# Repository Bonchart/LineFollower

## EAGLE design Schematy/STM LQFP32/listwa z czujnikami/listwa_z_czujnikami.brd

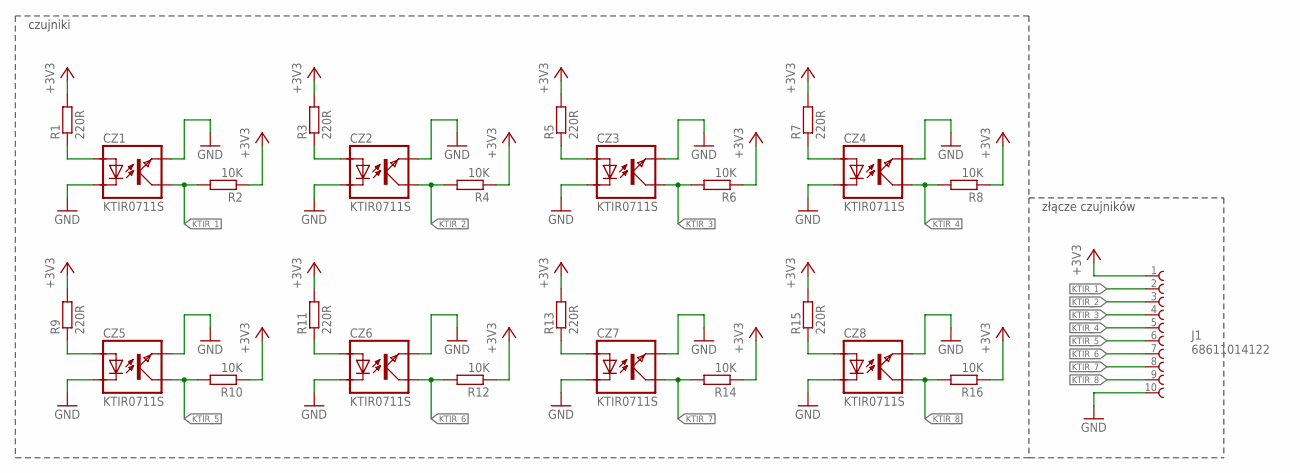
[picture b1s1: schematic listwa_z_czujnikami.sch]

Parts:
CZ1, CZ2, CZ3, CZ4, CZ5, CZ6, CZ7, CZ8: KTIR0711S; TOP
J1: 68611014122
R1, R3, R5, R7, R9, R11, R13, R15: 220R; R0805
R2, R4, R6, R8, R10, R12, R14, R16: 10K; R0805

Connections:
+3V3: J1.1, R1.2, R2.1, R3.2, R4.1, R5.2, R6.1, R7.2, R8.1, R9.2, R10.1, R11.2, R12.1, R13.2, R14.1, R15.2, R16.1
GND: CZ1.EMITER, CZ1.KATODA, CZ2.EMITER, CZ2.KATODA, CZ3.EMITER, CZ3.KATODA, CZ4.EMITER, CZ4.KATODA, CZ5.EMITER, CZ5.KATODA, CZ6.EMITER, CZ6.KATODA, CZ7.EMITER, CZ7.KATODA, CZ8.EMITER, CZ8.KATODA, J1.10
KTIR_1: CZ1.KOLEKTOR, J1.2, R2.2
KTIR_2: CZ2.KOLEKTOR, J1.3, R4.2
KTIR_3: CZ3.KOLEKTOR, J1.4, R6.2
KTIR_4: CZ4.KOLEKTOR, J1.5, R8.2
KTIR_5: CZ5.KOLEKTOR, J1.6, R10.2
KTIR_6: CZ6.KOLEKTOR, J1.7, R12.2
KTIR_7: CZ7.KOLEKTOR, J1.8, R14.2
KTIR_8: CZ8.KOLEKTOR, J1.9, R16.2
unnamed: CZ2.ANODA, R3.1
unnamed: CZ1.ANODA, R1.1
unnamed: CZ3.ANODA, R5.1
unnamed: CZ4.ANODA, R7.1
unnamed: CZ5.ANODA, R9.1
unnamed: CZ6.ANODA, R11.1
unnamed: CZ7.ANODA, R13.1
unnamed: CZ8.ANODA, R15.1

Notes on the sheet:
czujniki
złącze czujników

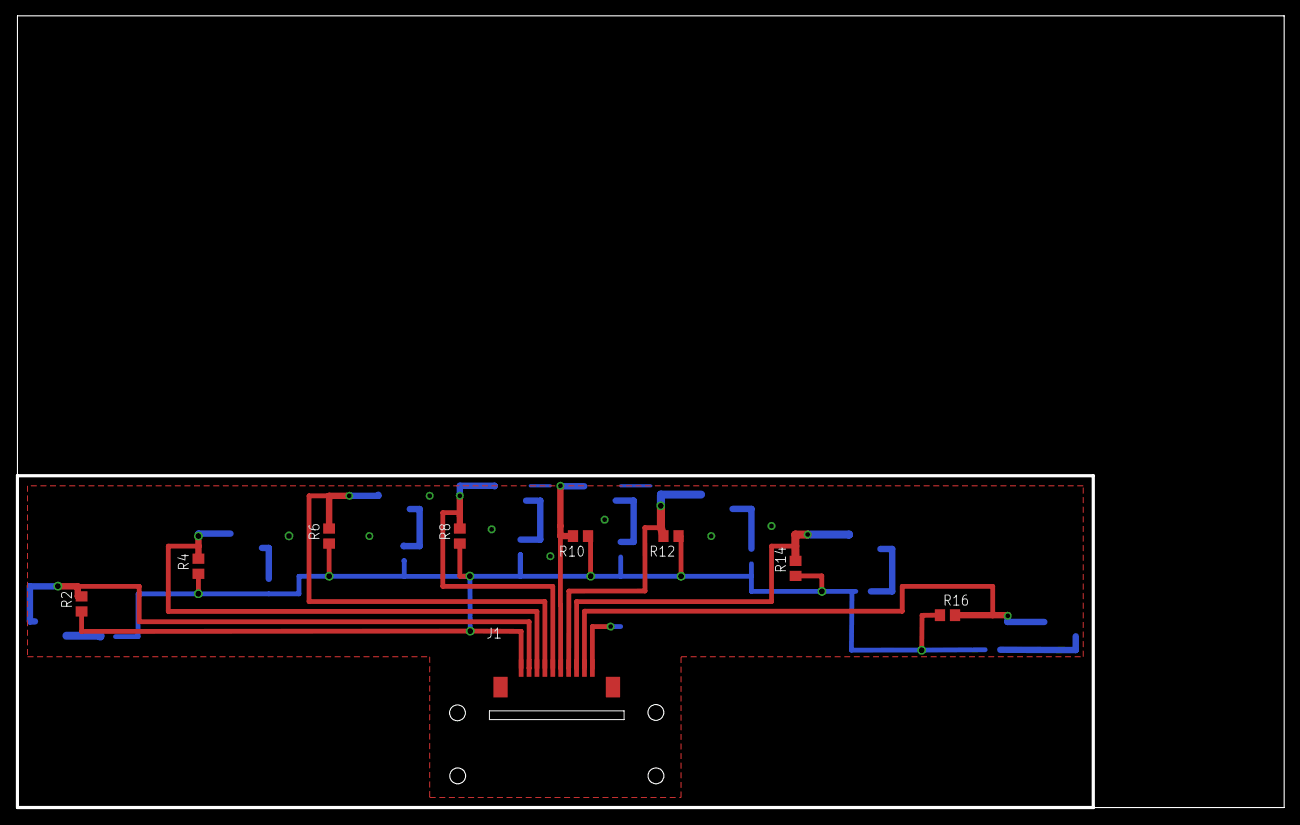
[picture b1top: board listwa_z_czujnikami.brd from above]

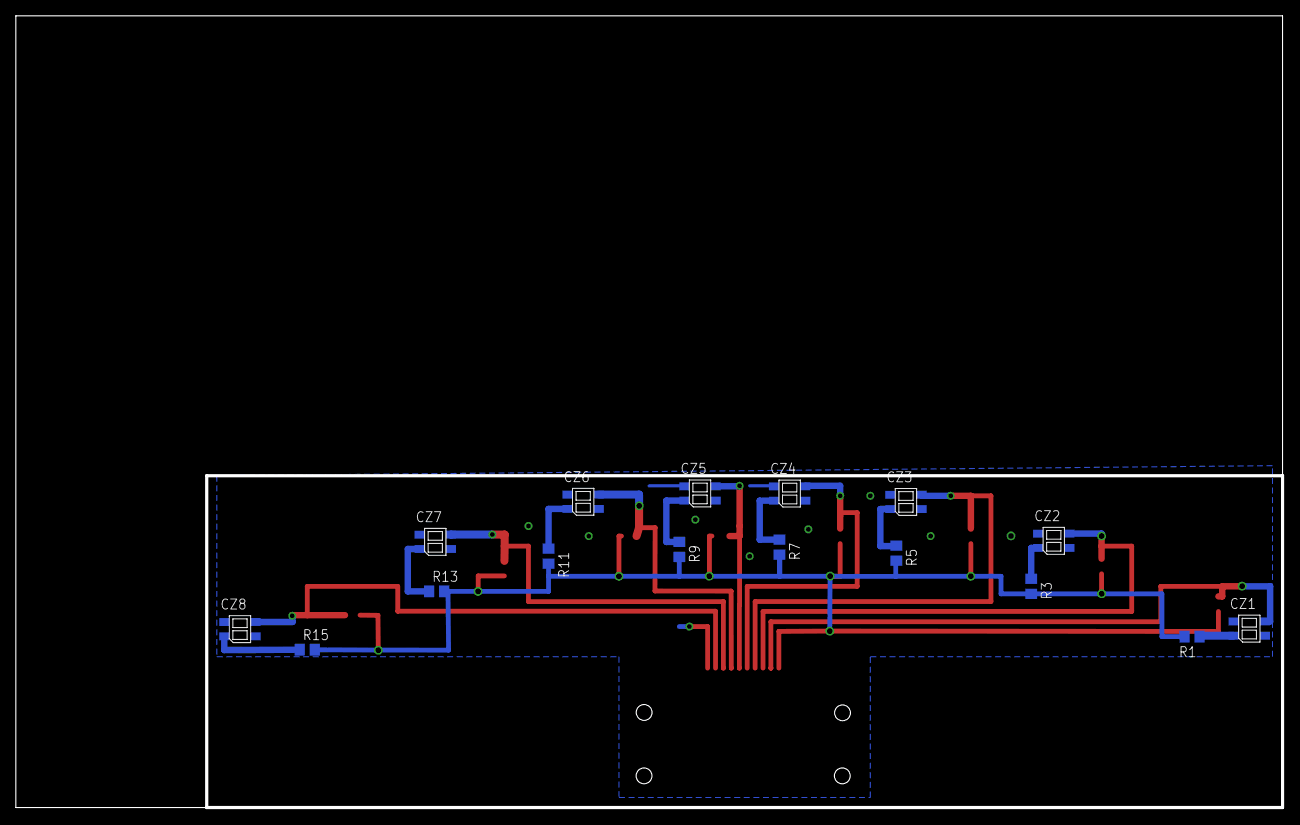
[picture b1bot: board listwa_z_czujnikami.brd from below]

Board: 2 copper layers, 160.0 x 100.0 mm, 25 parts (16 on the bottom side), 18 nets.

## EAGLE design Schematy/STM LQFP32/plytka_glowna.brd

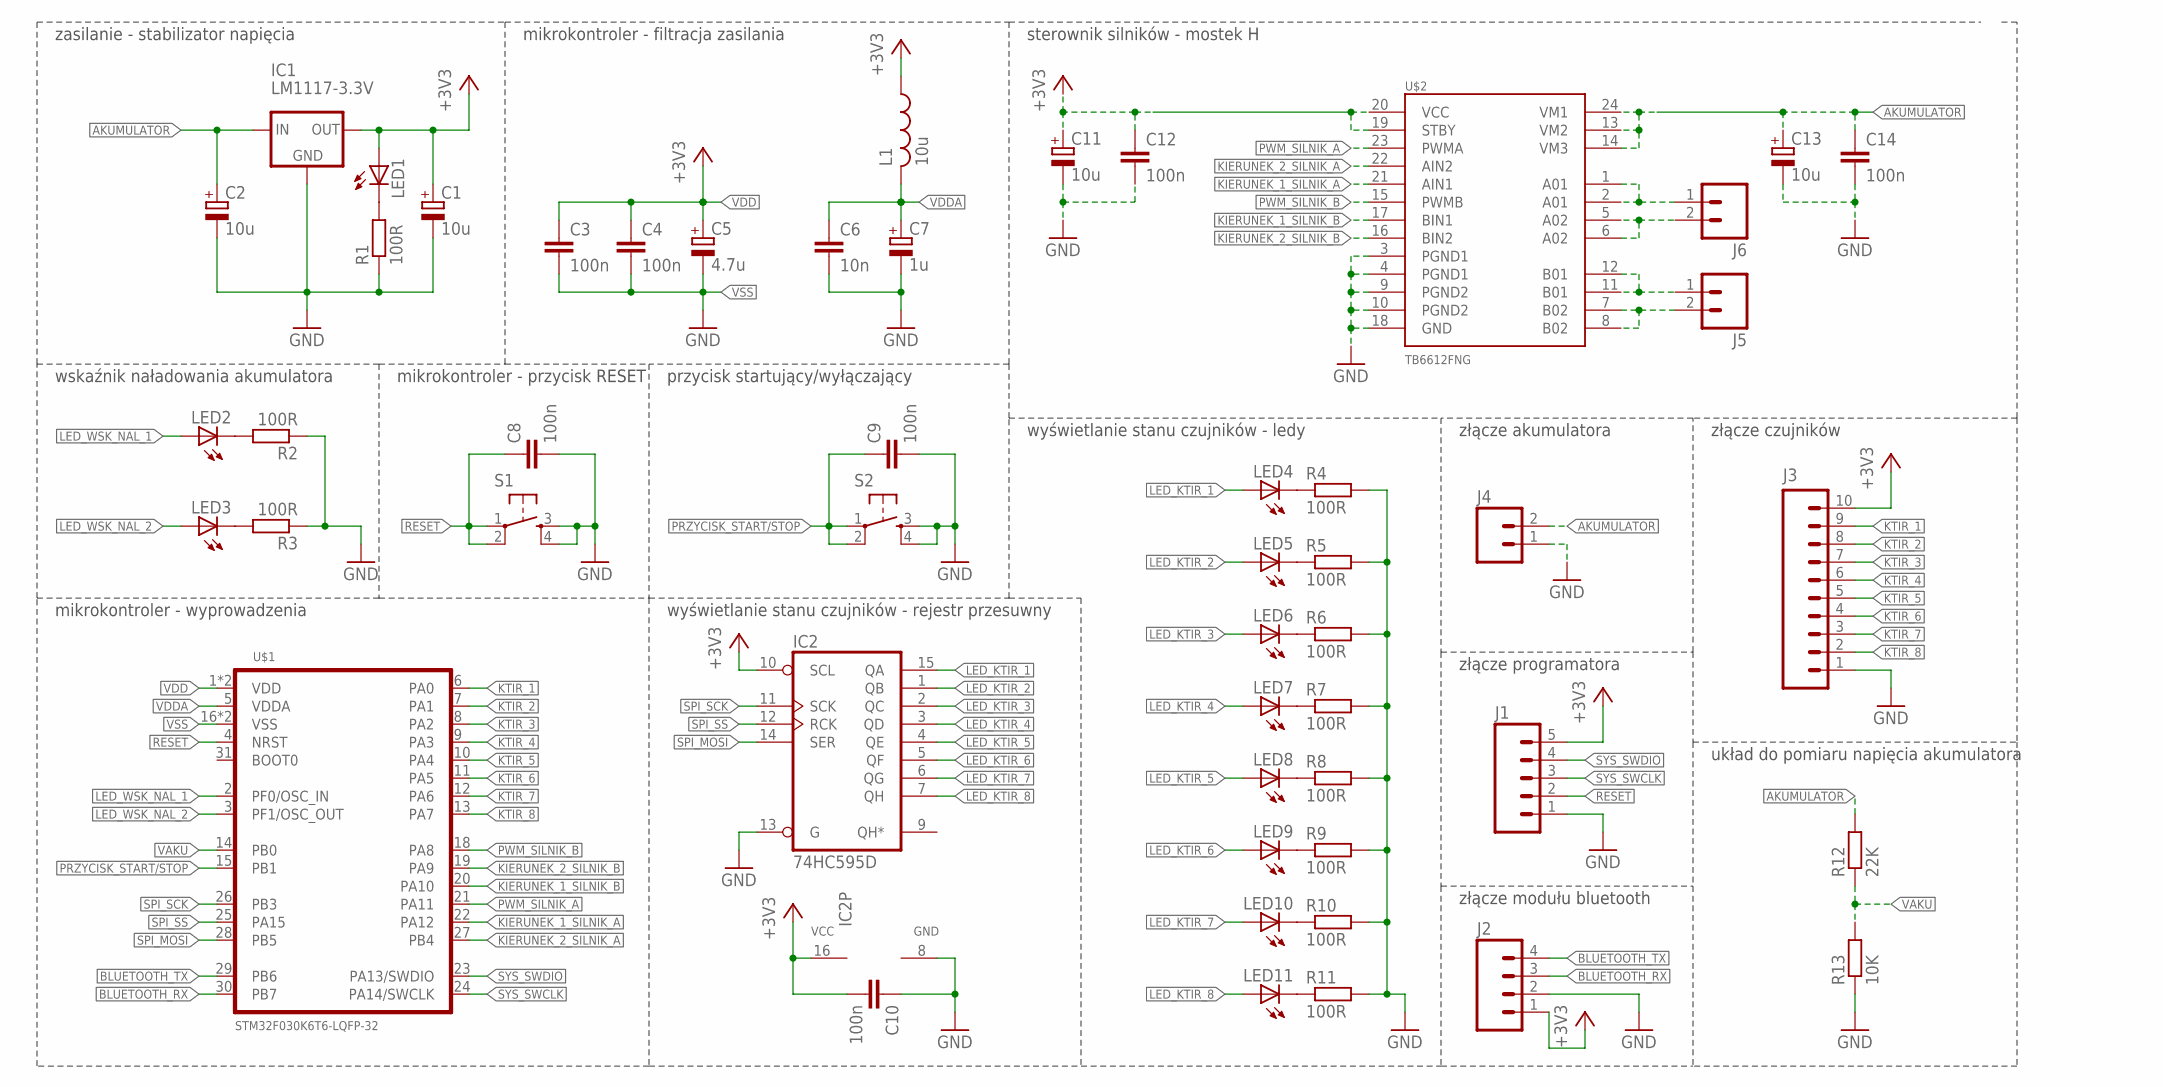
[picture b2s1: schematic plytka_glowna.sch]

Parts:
C1, C2, C11, C13: 10u; 085CS_1AR
C3, C4, C8, C9, C10, C12, C14: 100n; C025-024X044
C5: 4.7u; 085CS_1AR
C6: 10n; C025-024X044
C7: 1u; 085CS_1AR
IC1: LM1117-3.3V; TO252
IC2: 74HC595D; SO16
J1: M05LOCK_LONGPADS; 1X05_LOCK_LONGPADS
J2: M04JST; 1X04-1.5MM_JST
J3: M10LOCK; 1X10_LOCK
J4, J5, J6: M02-JST-2-PTH-NO_SILK; JST-2-PTH-NS
L1: 10u; 0204/5
LED1, LED2, LED3, LED4, LED5, LED6, LED7, LED8, LED9, LED10, LED11: LEDCHIP-LED0805; CHIP-LED0805
R1, R2, R3, R4, R5, R6, R7, R8, R9, R10, R11: 100R; 0204V
R12: 22K; 0204V
R13: 10K; 0204V
S1, S2: TACTILE-SWITCH-7914G; 7914G
U$1: STM32F030K6T6-LQFP-32; LQFP-32
U$2: TB6612FNG; SSOP24

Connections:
+3V3: C1.+, C10.2, IC1.TAB (OUT), IC2.10 (SCL), IC2.16 (VCC), J1.5, J2.1, J3.10, L1.1, LED1.A
AKUMULATOR: C2.+, C13.+, C14.1, IC1.2 (IN), J4.2, R12.2, U$2.13 (VM2), U$2.14 (VM3), U$2.24 (VM1)
BLUETOOTH_RX: J2.3, U$1.30 (PB7)
BLUETOOTH_TX: J2.4, U$1.29 (PB6)
GND: C1.-, C2.-, C6.2, C7.-, C8.2, C9.2, C10.1, C11.-, C12.2, C13.-, C14.2, IC1.1 (GND), IC2.8 (GND), IC2.13 (G), J1.1, J2.2, J3.1, J4.1, R1.1, R2.1, R3.1, R4.2, R5.2, R6.2, R7.2, R8.2, R9.2, R10.2, R11.2, R13.1, S1.3, S1.4, S2.3, S2.4, U$2.3 (PGND1), U$2.4 (PGND1), U$2.9 (PGND2), U$2.10 (PGND2), U$2.18 (GND)
KIERUNEK_1_SILNIK_A: U$1.22 (PA12), U$2.21 (AIN1)
KIERUNEK_1_SILNIK_B: U$1.20 (PA10), U$2.17 (BIN1)
KIERUNEK_2_SILNIK_A: U$1.27 (PB4), U$2.22 (AIN2)
KIERUNEK_2_SILNIK_B: U$1.19 (PA9), U$2.16 (BIN2)
KTIR_1: J3.9, U$1.6 (PA0)
KTIR_2: J3.8, U$1.7 (PA1)
KTIR_3: J3.7, U$1.8 (PA2)
KTIR_4: J3.6, U$1.9 (PA3)
KTIR_5: J3.5, U$1.10 (PA4)
KTIR_6: J3.4, U$1.11 (PA5)
KTIR_7: J3.3, U$1.12 (PA6)
KTIR_8: J3.2, U$1.13 (PA7)
LED_KTIR_1: IC2.15 (QA), LED4.A
LED_KTIR_2: IC2.1 (QB), LED5.A
LED_KTIR_3: IC2.2 (QC), LED6.A
LED_KTIR_4: IC2.3 (QD), LED7.A
LED_KTIR_5: IC2.4 (QE), LED8.A
LED_KTIR_6: IC2.5 (QF), LED9.A
LED_KTIR_7: IC2.6 (QG), LED10.A
LED_KTIR_8: IC2.7 (QH), LED11.A
LED_WSK_NAL_1: LED2.A, U$1.2 (PF0/OSC_IN)
LED_WSK_NAL_2: LED3.A, U$1.3 (PF1/OSC_OUT)
unnamed: LED1.C, R1.2
unnamed: LED2.C, R2.2
unnamed: LED3.C, R3.2
unnamed: LED4.C, R4.1
unnamed: LED5.C, R5.1
unnamed: J6.2, U$2.5 (A02), U$2.6 (A02)
unnamed: J5.2, U$2.7 (B02), U$2.8 (B02)
unnamed: LED6.C, R6.1
unnamed: J5.1, U$2.11 (B01), U$2.12 (B01)
unnamed: LED7.C, R7.1
unnamed: J6.1, U$2.1 (A01), U$2.2 (A01)
unnamed: LED8.C, R8.1
unnamed: LED9.C, R9.1
unnamed: LED10.C, R10.1
unnamed: LED11.C, R11.1
PRZYCISK_START/STOP: C9.1, S2.1, S2.2, U$1.15 (PB1)
PWM_SILNIK_A: U$1.21 (PA11), U$2.23 (PWMA)
PWM_SILNIK_B: U$1.18 (PA8), U$2.15 (PWMB)
RESET: C8.1, J1.2, S1.1, S1.2, U$1.4 (NRST)
SPI_MOSI: IC2.14 (SER), U$1.28 (PB5)
SPI_SCK: IC2.11 (SCK), U$1.26 (PB3)
SPI_SS: IC2.12 (RCK), U$1.25 (PA15)
SYS_SWCLK: J1.3, U$1.24 (PA14/SWCLK)
SYS_SWDIO: J1.4, U$1.23 (PA13/SWDIO)
TB6612_VCC: C11.+, C12.1, U$2.19 (STBY), U$2.20 (VCC)
VAKU: R12.1, R13.2, U$1.14 (PB0)
VDD: C3.1, C4.1, C5.+, U$1.1 (VDD), U$1.17 (VDD)
VDDA: C6.1, C7.+, L1.2, U$1.5 (VDDA)
VSS: C3.2, C4.2, C5.-, U$1.16 (VSS), U$1.32 (VSS)

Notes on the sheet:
mikrokontroler - wyprowadzenia
wskaźnik naładowania akumulatora
mikrokontroler - przycisk RESET
mikrokontroler - filtracja zasilania
zasilanie - stabilizator napięcia
przycisk startujący/wyłączający
wyświetlanie stanu czujników - rejestr przesuwny
wyświetlanie stanu czujników - ledy
złącze modułu bluetooth
złącze programatora
układ do pomiaru napięcia akumulatora
złącze czujników
sterownik silników - mostek H
złącze akumulatora

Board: 2 copper layers, 51 parts (0 on the bottom side), 56 nets, no tracks yet.

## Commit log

2016-10-26 test1
2016-10-26 Revert "first commit"
    This reverts commit a0719614e6ed53f7bf627719ab25c89f8cac89a8.
2016-10-26 zmiana
2016-10-26 galaz
2016-10-26 Merge branch 'master' into judyta
    # Conflicts:
    # TEST.txt
2016-10-26 nazwa
2016-10-26 zmiana00
2016-11-01 Delete K
    robię porządek
2016-11-01 Delete TEST.txt
    robię porządek
2016-11-01 Test. Schemat mostka H
    Test pracy na gicie. Wrzucam pliki projektu ze schematem mostka H
2016-11-01 test.projekt
2016-11-02 czy doda folder?
2016-11-02 Schematy [folder właściwy]
    Niech to będzie folder ze schematami. Kolejne zmiany będę dodawał przez nową gałąź.
2016-11-02 Rozpoczęty schemat płyty głównej [mostek H]
2016-11-02 Płyta główna + listwa - do sprawdzenia
    do zrobienia układ pomiarowy obniżający napięcie z akumulatora do tolerowanego przez uC, dobranie złącz
2016-11-02 Płyta główna + listwa [do sprawdzenia]
    do zrobienia:
    - układ pomiarowy napięcia na akumulatorze
    - wskaźnik naładowania akumulatora na 3 led
    - dobrać złącza
    - zagospodarować pozostałe piny
2016-11-03 Kompletny schemat elektryczny [do sprawdzenia]
2016-11-04 Schemat elektryczny
    @edit
    zmiana modułu bluetooth z HC-05 na HC-06
2016-11-05 Dorzucam schemat w Eagledla STM32 w obudowie LQFP32
2016-11-06 Lista elementów
2016-11-06 Płytka główna + listwa z czujnikami
    * dodałem listwę z czujnikami
    * poprawiłem cewkę przy mikrokontrolerze
    * zmieniłem złącze czujników na 1x10
    * poprawiłem złącze do modułu bluetooth
2016-11-07 Złącze FFC
2016-11-07 Add files via upload
    Listwa FFC
2016-11-17 Płytka gotowa
2016-11-17 poprawiona płytka główna
2016-11-19 Listwa koniec
2016-11-22 Poprawione PCB
2016-11-23 Posprzątane

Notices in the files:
parts and their libraries:
FPC_Connectors_Flat_Flexible_Cable_rev15: Copyright: Würth Elektronik
SparkFun-Connectors: Licensing: Creative Commons ShareAlike 4.0 International - https://creativecommons.org/licenses/by-sa/4.0
